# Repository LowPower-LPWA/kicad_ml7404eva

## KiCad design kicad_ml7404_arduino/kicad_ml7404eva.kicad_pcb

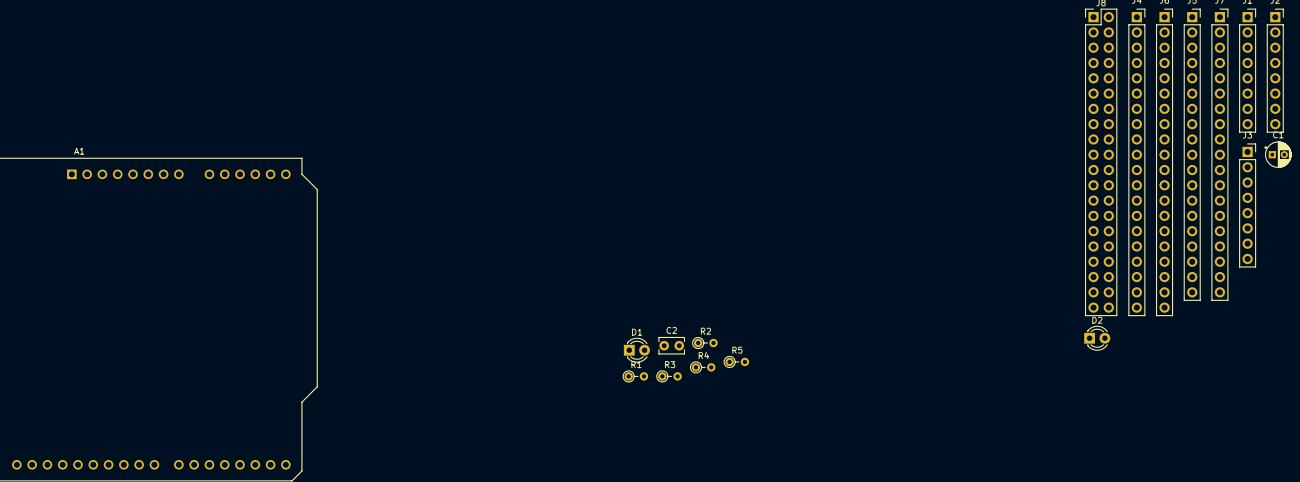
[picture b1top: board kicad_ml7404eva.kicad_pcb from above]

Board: 2 copper layers, 18 parts (0 on the bottom side), 16 nets, no tracks yet.

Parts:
A1: Arduino_UNO_R3
C1: C; CP_Radial_D4.0mm_P2.00mm
C2: CP; C_Rect_L4.0mm_W2.5mm_P2.50mm
D1, D2: LED; LED_D3.0mm
J1, J2, J3: Conn_01x08_Female; PinSocket_1x08_P2.54mm_Vertical
J4, J6: Conn_01x20_Female; PinSocket_1x20_P2.54mm_Vertical
J5, J7: Conn_01x19_Female; PinSocket_1x19_P2.54mm_Vertical
J8: Raspberry_Pi_2_3; PinHeader_2x20_P2.54mm_Vertical
R1, R2: 1k; R_Axial_DIN0204_L3.6mm_D1.6mm_P2.54mm_Vertical
R3, R4, R5: 10k; R_Axial_DIN0204_L3.6mm_D1.6mm_P2.54mm_Vertical

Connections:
+3V3: A1.4, C1.1, C2.1, J2.1, J5.1, J6.16, J8.1, J8.17, R1.1, R2.1, R3.1, R4.1, R5.1
GND: A1.6, A1.7, A1.29, C1.2, C2.2, J2.2, J3.4, J3.5, J4.3, J4.8, J4.13, J4.18, J5.2, J5.14, J6.3, J6.8, J6.13, J6.18, J7.13, J7.19, J8.6, J8.9, J8.14, J8.20, J8.25, J8.30, J8.34, J8.39
LEDRX: A1.22, D2.1, J4.15, J5.4, J8.33
LEDTX: A1.21, D1.1, J4.14, J5.3, J8.31
MISO: A1.27, J1.1, J4.6, J5.13, J8.21
MOSI: A1.26, J1.4, J4.5, J5.15, J8.19
unnamed: D1.2, R1.2
unnamed: D2.2, R2.2
REGPDIN: A1.19, J2.8, J4.10, J5.7, J8.11
RESETN: A1.18, J2.7, J4.9, J5.6, J8.13
SCEN: A1.25, J1.3, J7.4, J8.24
SCL: A1.32, J3.7, J7.17, J8.5, R4.2
SCLK: A1.28, J1.2, J4.4, J5.12, J8.23
SDA: A1.31, J3.8, J7.14, J8.3, R5.2
SINTN: A1.17, J1.5, J4.16, J5.5, J8.12
WP: A1.20, J3.6, R3.2

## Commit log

2021-03-26 temporary update
2021-03-27 MCU別に基板を分割
